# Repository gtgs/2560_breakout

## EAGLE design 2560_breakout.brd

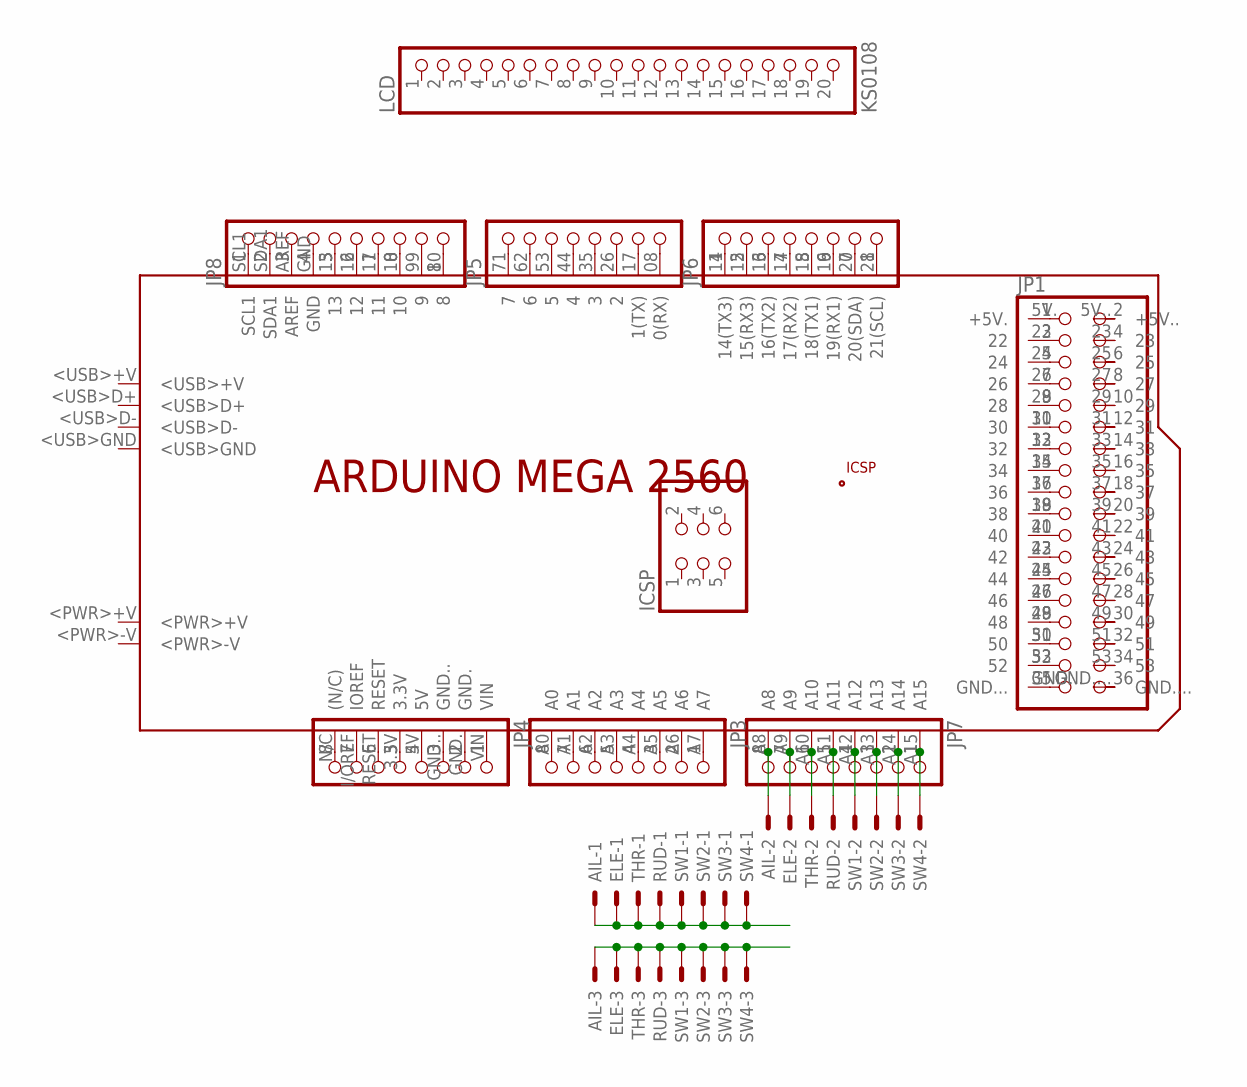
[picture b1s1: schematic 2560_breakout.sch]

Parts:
AIL: JST-XH-03-PIN-LONG-PAD; JST-XH-03-PACKAGE-LONG-PAD
ELE: JST-XH-03-PIN-LONG-PAD; JST-XH-03-PACKAGE-LONG-PAD
ICSP: PINHD-2X3; 2X03
JP1: PINHD-2X18; 2X18
JP3, JP4, JP5, JP6, JP7: PINHD-1X8; 1X08
JP8: PINHD-1X10; 1X10
LCD: KS0108; 1X20
PCB1: ARDUINO_MEGA2560
RUD: JST-XH-03-PIN-LONG-PAD; JST-XH-03-PACKAGE-LONG-PAD
SW1, SW2, SW3, SW4: JST-XH-03-PIN-LONG-PAD; JST-XH-03-PACKAGE-LONG-PAD
THR: JST-XH-03-PIN-LONG-PAD; JST-XH-03-PACKAGE-LONG-PAD

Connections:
unnamed: JP1.1, PCB1.5V. (+5V.)
unnamed: JP1.3, PCB1.22
unnamed: JP1.5, PCB1.24
unnamed: JP1.7, PCB1.26
unnamed: JP1.9, PCB1.28
unnamed: JP1.11, PCB1.30
unnamed: JP1.13, PCB1.32
unnamed: JP1.15, PCB1.34
unnamed: JP1.17, PCB1.36
unnamed: JP1.19, PCB1.38
unnamed: JP1.21, PCB1.40
unnamed: JP1.23, PCB1.42
unnamed: JP1.25, PCB1.44
unnamed: JP1.27, PCB1.46
unnamed: JP1.29, PCB1.48
unnamed: JP1.31, PCB1.50
unnamed: JP1.33, PCB1.52
unnamed: JP1.35, PCB1.GND...
unnamed: JP6.1, PCB1.14 (14(TX3))
unnamed: JP6.2, PCB1.15 (15(RX3))
unnamed: JP6.3, PCB1.16 (16(TX2))
unnamed: JP6.4, PCB1.17 (17(RX2))
unnamed: JP6.5, PCB1.18 (18(TX1))
unnamed: JP6.6, PCB1.19 (19(RX1))
unnamed: JP6.7, PCB1.20 (20(SDA))
unnamed: JP6.8, PCB1.21 (21(SCL))
unnamed: JP5.1, PCB1.7
unnamed: JP5.2, PCB1.6
unnamed: JP5.3, PCB1.5
unnamed: JP5.4, PCB1.4
unnamed: JP5.5, PCB1.3
unnamed: JP5.6, PCB1.2
unnamed: JP5.7, PCB1.1 (1(TX))
unnamed: JP5.8, PCB1.0 (0(RX))
unnamed: JP8.1, PCB1.SCL1
unnamed: JP8.2, PCB1.SDA1
unnamed: JP8.3, PCB1.AREF
unnamed: JP8.4, PCB1.GND
unnamed: JP8.5, PCB1.13
unnamed: JP8.6, PCB1.12
unnamed: JP8.7, PCB1.11
unnamed: JP8.8, PCB1.10
unnamed: JP8.9, PCB1.9
unnamed: JP8.10, PCB1.8
unnamed: JP4.1, PCB1.VIN
unnamed: JP4.2, PCB1.GND.
unnamed: JP4.3, PCB1.GND..
unnamed: JP4.4, PCB1.5V
unnamed: JP4.5, PCB1.3.3V
unnamed: JP4.6, PCB1.RESET
unnamed: JP4.7, PCB1.I/OREF (IOREF)
unnamed: JP4.8, PCB1.N/C ((N/C))
unnamed: JP3.1, PCB1.A7
unnamed: JP3.2, PCB1.A6
unnamed: JP3.3, PCB1.A5
unnamed: JP3.4, PCB1.A4
unnamed: JP3.5, PCB1.A3
unnamed: JP3.6, PCB1.A2
unnamed: JP3.7, PCB1.A1
unnamed: JP3.8, PCB1.A0
unnamed: JP7.1, PCB1.A15, SW4.2
unnamed: JP7.2, PCB1.A14, SW3.2
unnamed: JP7.3, PCB1.A13, SW2.2
unnamed: JP7.4, PCB1.A12, SW1.2
unnamed: JP7.5, PCB1.A11, RUD.2
unnamed: JP7.6, PCB1.A10, THR.2
unnamed: ELE.2, JP7.7, PCB1.A9
unnamed: AIL.2, JP7.8, PCB1.A8
unnamed: AIL.1, ELE.1, RUD.1, SW1.1, SW2.1, SW3.1, SW4.1, THR.1
unnamed: AIL.3, ELE.3, RUD.3, SW1.3, SW2.3, SW3.3, SW4.3, THR.3

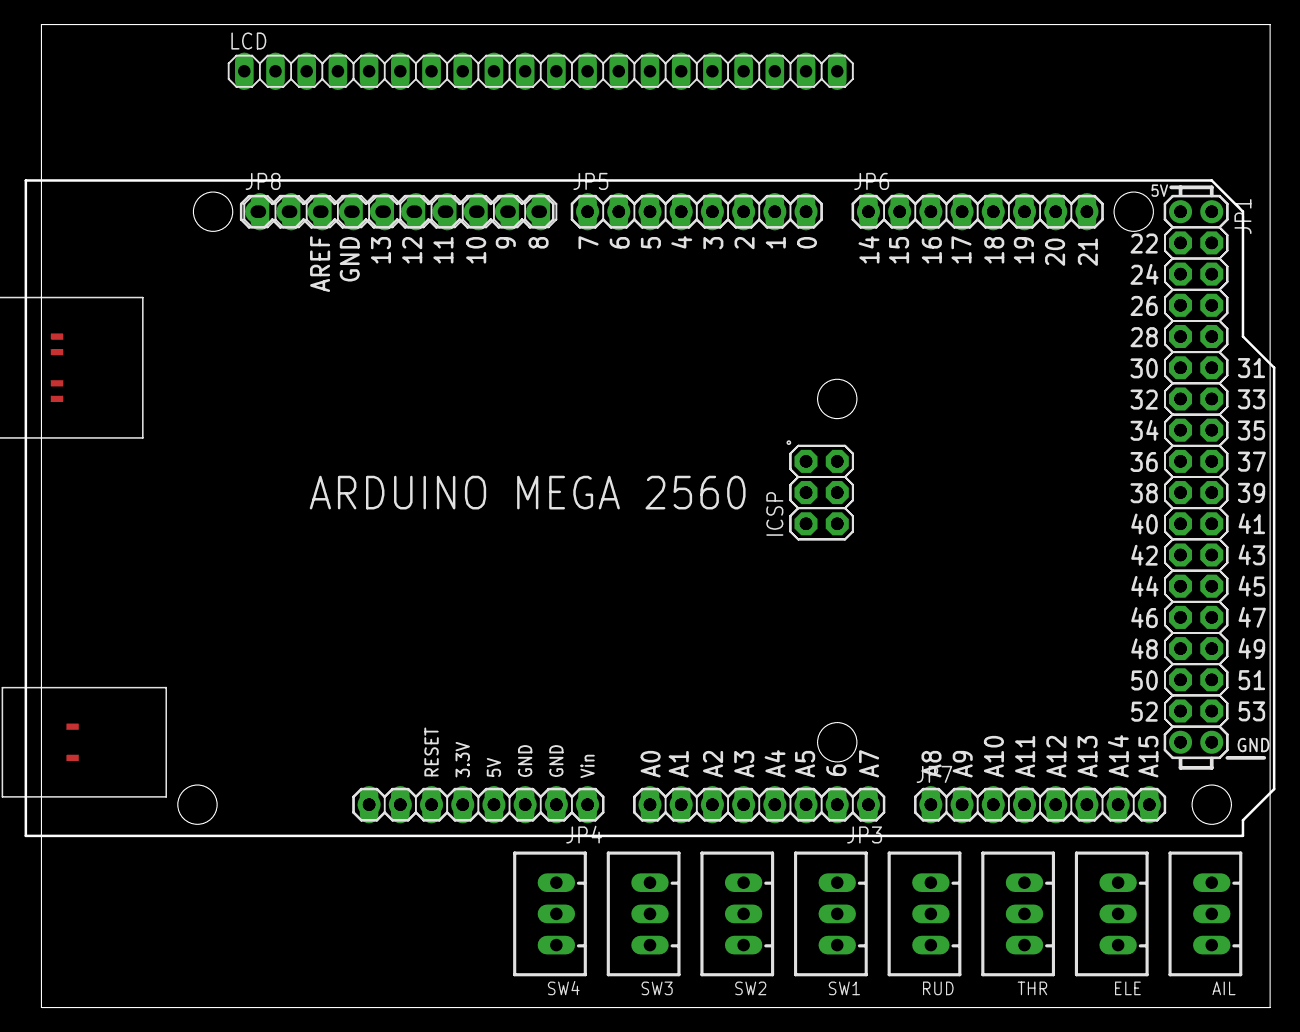
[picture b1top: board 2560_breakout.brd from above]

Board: 2 copper layers, 101.6 x 79.8 mm, 18 parts (0 on the bottom side), 70 nets.
